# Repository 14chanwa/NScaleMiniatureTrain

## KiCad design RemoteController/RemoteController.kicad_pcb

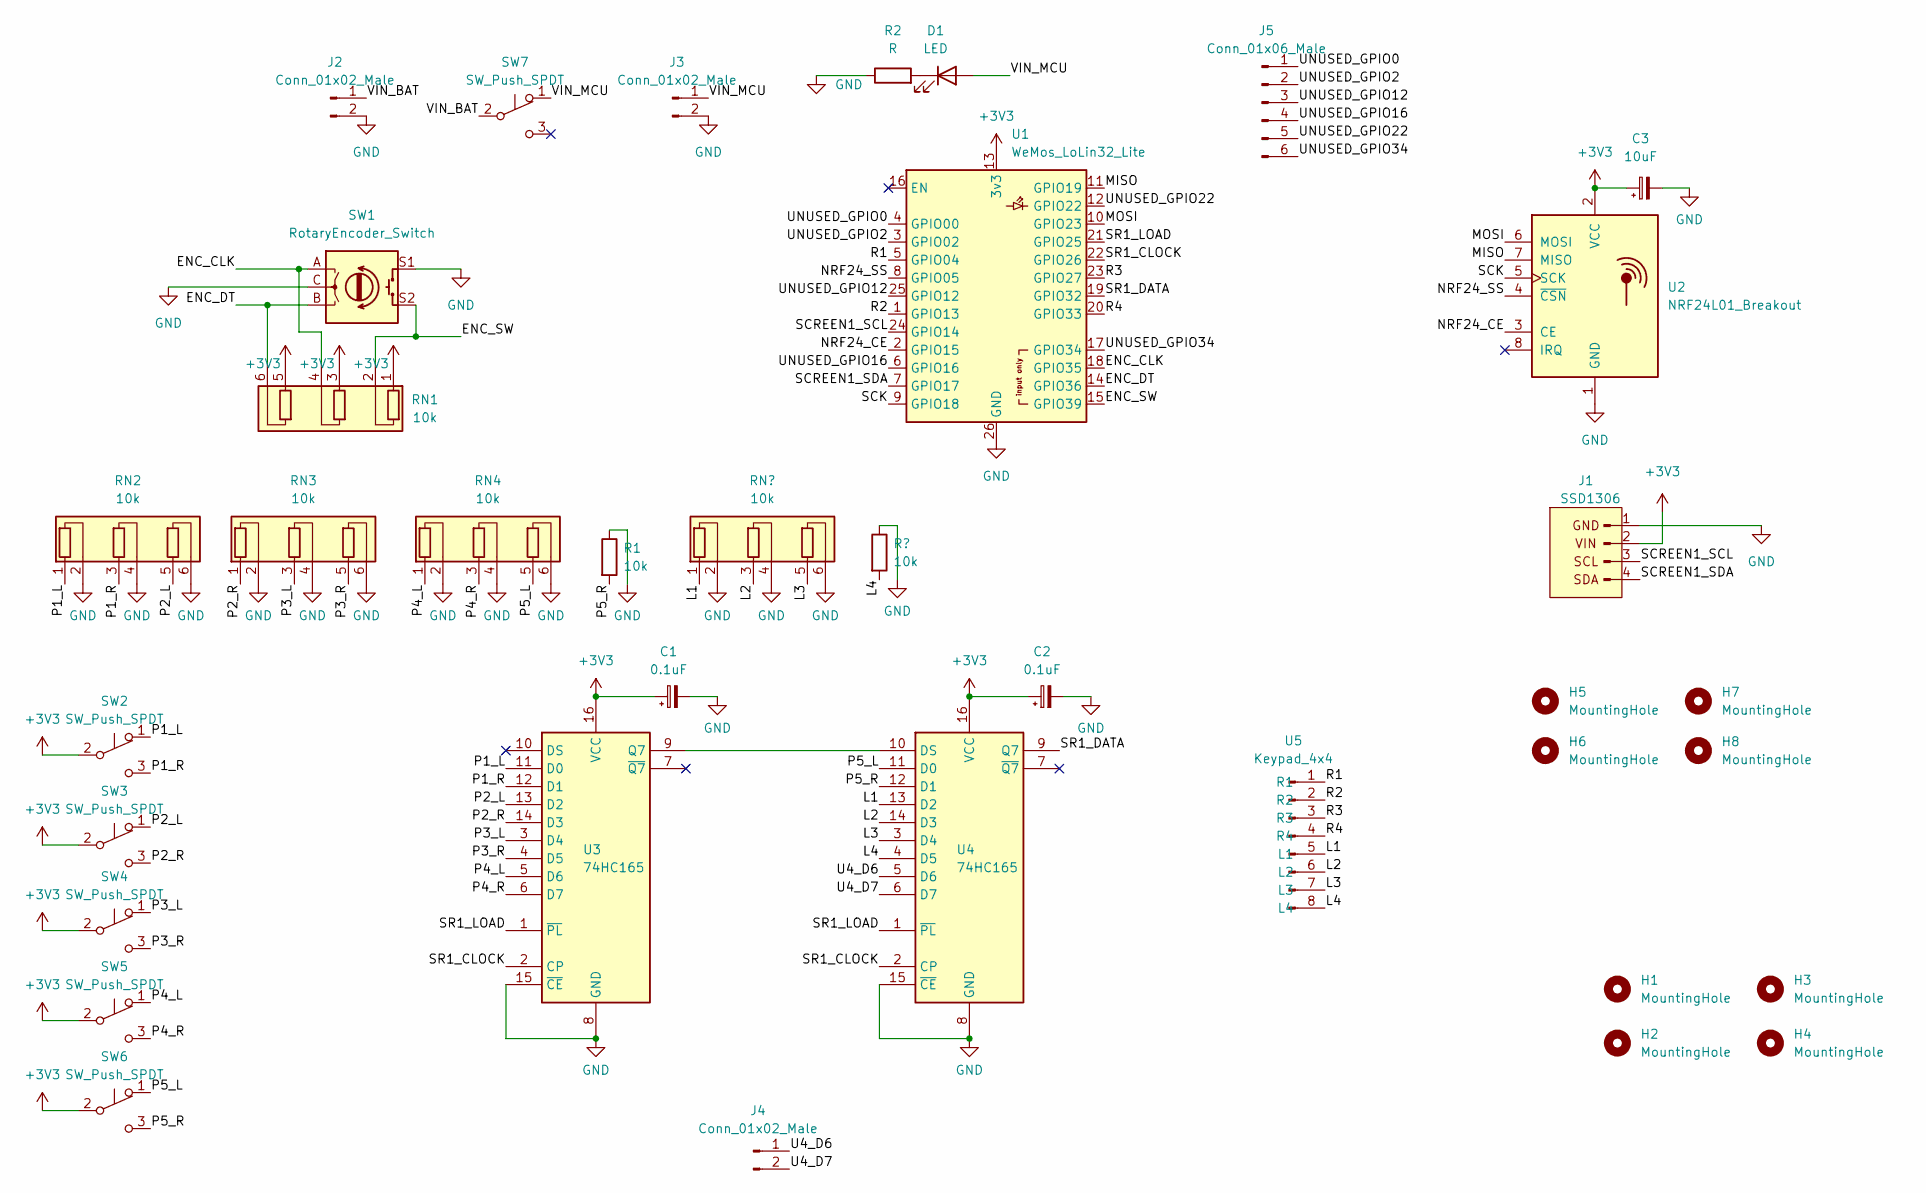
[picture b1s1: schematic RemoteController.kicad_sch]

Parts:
C1, C2: 0.1uF; CP_Radial_D4.0mm_P2.00mm
C3: 10uF; CP_Radial_D4.0mm_P2.00mm
D1: LED; LED_D3.0mm
H1, H2, H3, H4: MountingHole; MountingHole_2.5mm
H5, H6, H7, H8: MountingHole; MountingHole_4.3mm_M4_DIN965
J1: SSD1306; 128x64OLED
J2: Conn_01x02_Male; JST_PH_B2B-PH-K_1x02_P2.00mm_Vertical
J3: Conn_01x02_Male; PinHeader_1x02_P2.54mm_Vertical
J4: Conn_01x02_Male; PinSocket_1x02_P2.54mm_Vertical
J5: Conn_01x06_Male; PinSocket_1x06_P2.54mm_Vertical
R1: 10k; R_Axial_DIN0207_L6.3mm_D2.5mm_P10.16mm_Horizontal
R2: R; R_Axial_DIN0207_L6.3mm_D2.5mm_P10.16mm_Horizontal
RN1, RN2, RN3, RN4: 10k; R_Array_SIP6
SW1: RotaryEncoder_Switch; RotaryEncoder_Alps_EC12E-Switch_Vertical_H20mm
SW2, SW3, SW4, SW5, SW6, SW7: SW_Push_SPDT; Switch6mm
U1: WeMos_LoLin32_Lite; WEMOS_LoLin32_Lite
U2: NRF24L01_Breakout; nRF24L01_Breakout
U3, U4: 74HC165; SOP-16_4.4x10.4mm_P1.27mm
U5: Keypad_4x4; Keypad

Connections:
+3V3: C1.1, C2.1, C3.1, J1.2, RN1.1 (R1.1), RN1.3 (R2.1), RN1.5 (R3.1), SW2.2 (B), SW3.2 (B), SW4.2 (B), SW5.2 (B), SW6.2 (B), U1.13 (3v3), U2.2 (VCC), U3.16 (VCC), U4.16 (VCC)
/ENC_CLK: RN1.4 (R2.2), SW1.A, U1.18 (GPIO35)
/ENC_DT: RN1.6 (R3.2), SW1.B, U1.14 (GPIO36)
/ENC_SW: RN1.2 (R1.2), SW1.S2, U1.15 (GPIO39)
/L1: U4.13 (D2), U5.5 (L1); also elsewhere on the board
/L2: U4.14 (D3), U5.6 (L2); also elsewhere on the board
/L3: U4.3 (D4), U5.7 (L3); also elsewhere on the board
/L4: U4.4 (D5), U5.8 (L4); also elsewhere on the board
/MISO: U1.11 (GPIO19), U2.7 (MISO)
/MOSI: U1.10 (GPIO23), U2.6 (MOSI)
/NRF24_CE: U1.2 (GPIO15), U2.3 (CE)
/NRF24_SS: U1.8 (GPIO05), U2.4 (~CSN)
/P1_L: RN2.1 (R1.1), SW2.1 (A), U3.11 (D0)
/P1_R: RN2.3 (R2.1), SW2.3 (C), U3.12 (D1)
/P2_L: RN2.5 (R3.1), SW3.1 (A), U3.13 (D2)
/P2_R: RN3.1 (R1.1), SW3.3 (C), U3.14 (D3)
/P3_L: RN3.3 (R2.1), SW4.1 (A), U3.3 (D4)
/P3_R: RN3.5 (R3.1), SW4.3 (C), U3.4 (D5)
/P4_L: RN4.1 (R1.1), SW5.1 (A), U3.5 (D6)
/P4_R: RN4.3 (R2.1), SW5.3 (C), U3.6 (D7)
/P5_L: RN4.5 (R3.1), SW6.1 (A), U4.11 (D0)
/P5_R: R1.2, SW6.3 (C), U4.12 (D1)
/R1: U1.5 (GPIO04), U5.1 (R1)
/R2: U1.1 (GPIO13), U5.2 (R2)
/R3: U1.23 (GPIO27), U5.3 (R3)
/R4: U1.20 (GPIO33), U5.4 (R4)
/SCK: U1.9 (GPIO18), U2.5 (SCK)
/SCREEN1_SCL: J1.3, U1.24 (GPIO14)
/SCREEN1_SDA: J1.4, U1.7 (GPIO17)
/SR1_CLOCK: U1.22 (GPIO26), U3.2 (CP), U4.2 (CP)
/SR1_DATA: U1.19 (GPIO32), U4.9 (Q7)
/SR1_LOAD: U1.21 (GPIO25), U3.1 (~PL), U4.1 (~PL)
/U4_D6: J4.1, U4.5 (D6)
/U4_D7: J4.2, U4.6 (D7)
/UNUSED_GPIO0: J5.1, U1.4 (GPIO00)
/UNUSED_GPIO2: J5.2, U1.3 (GPIO02)
/UNUSED_GPIO12: J5.3, U1.25 (GPIO12)
/UNUSED_GPIO16: J5.4, U1.6 (GPIO16)
/UNUSED_GPIO22: J5.5, U1.12 (GPIO22)
/UNUSED_GPIO34: J5.6, U1.17 (GPIO34)
/VIN_BAT: J2.1, SW7.2 (B)
/VIN_MCU: D1.2 (A), J3.1, SW7.1 (A)
GND: C1.2, C2.2, C3.2, J1.1, J2.2, J3.2, R1.1, R2.1, RN2.2 (R1.2), RN2.4 (R2.2), RN2.6 (R3.2), RN3.2 (R1.2), RN3.4 (R2.2), RN3.6 (R3.2), RN4.2 (R1.2), RN4.4 (R2.2), RN4.6 (R3.2), SW1.C, SW1.S1, U1.26 (GND), U2.1 (GND), U3.8 (GND), U3.15 (~CE), U4.8 (GND), U4.15 (~CE); also elsewhere on the board
unnamed: D1.1 (K), R2.2
unnamed: U3.9 (Q7), U4.10 (DS)

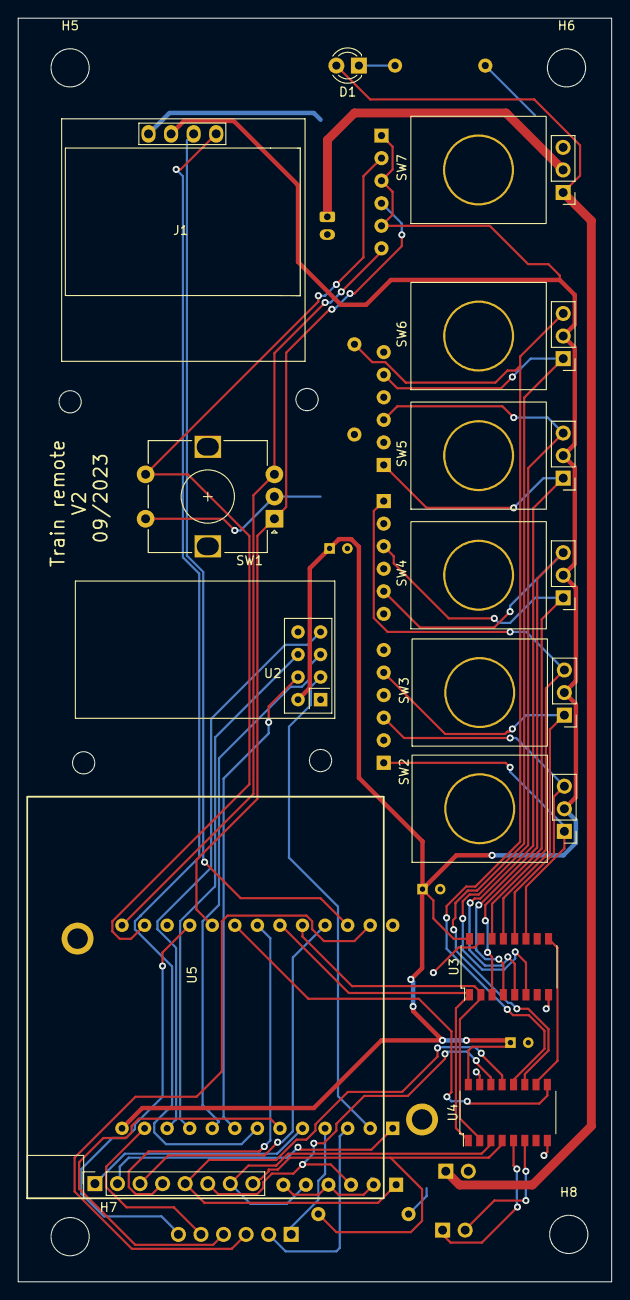
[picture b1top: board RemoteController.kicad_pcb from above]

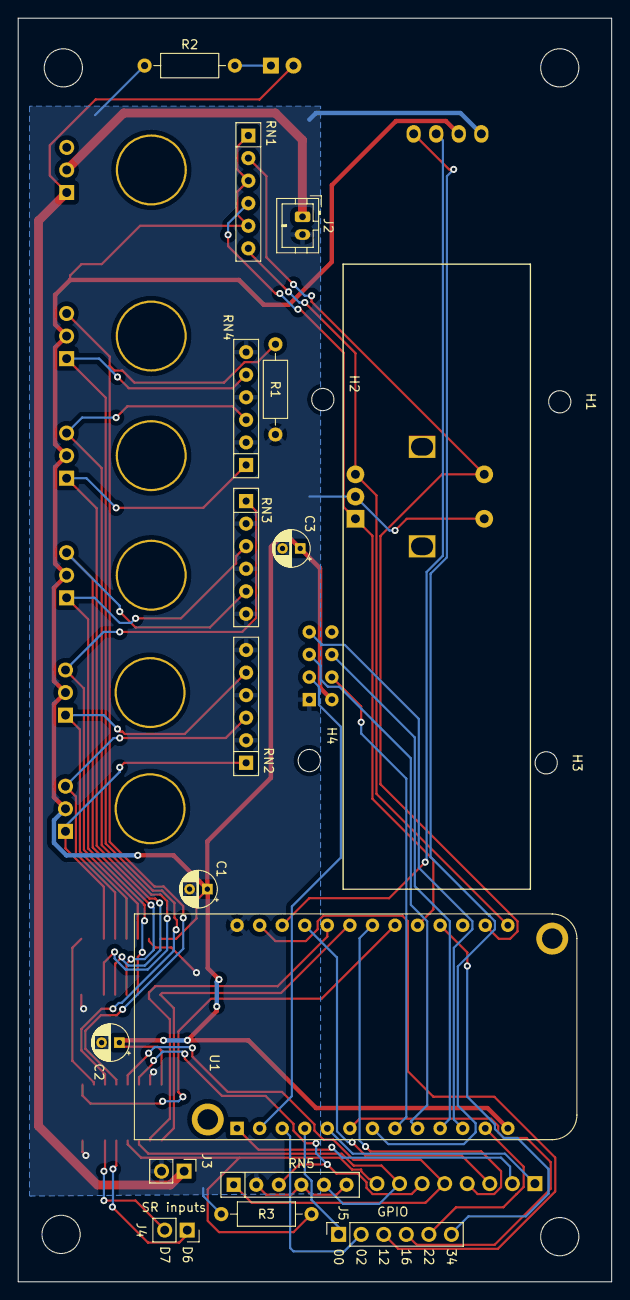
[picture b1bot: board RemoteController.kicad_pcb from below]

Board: 2 copper layers, 66.8 x 142.2 mm, 37 parts (20 on the bottom side), 45 nets.

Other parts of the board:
R3: 10k; R_Axial_DIN0207_L6.3mm_D2.5mm_P10.16mm_Horizontal
RN5: 10k; R_Array_SIP6

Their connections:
/L1: RN5.1 (R1.1); also elsewhere on the board
/L2: RN5.3 (R2.1); also elsewhere on the board
/L3: RN5.5 (R3.1); also elsewhere on the board
/L4: R3.2; also elsewhere on the board
GND: R3.1, RN5.2 (R1.2), RN5.4 (R2.2), RN5.6 (R3.2); also elsewhere on the board

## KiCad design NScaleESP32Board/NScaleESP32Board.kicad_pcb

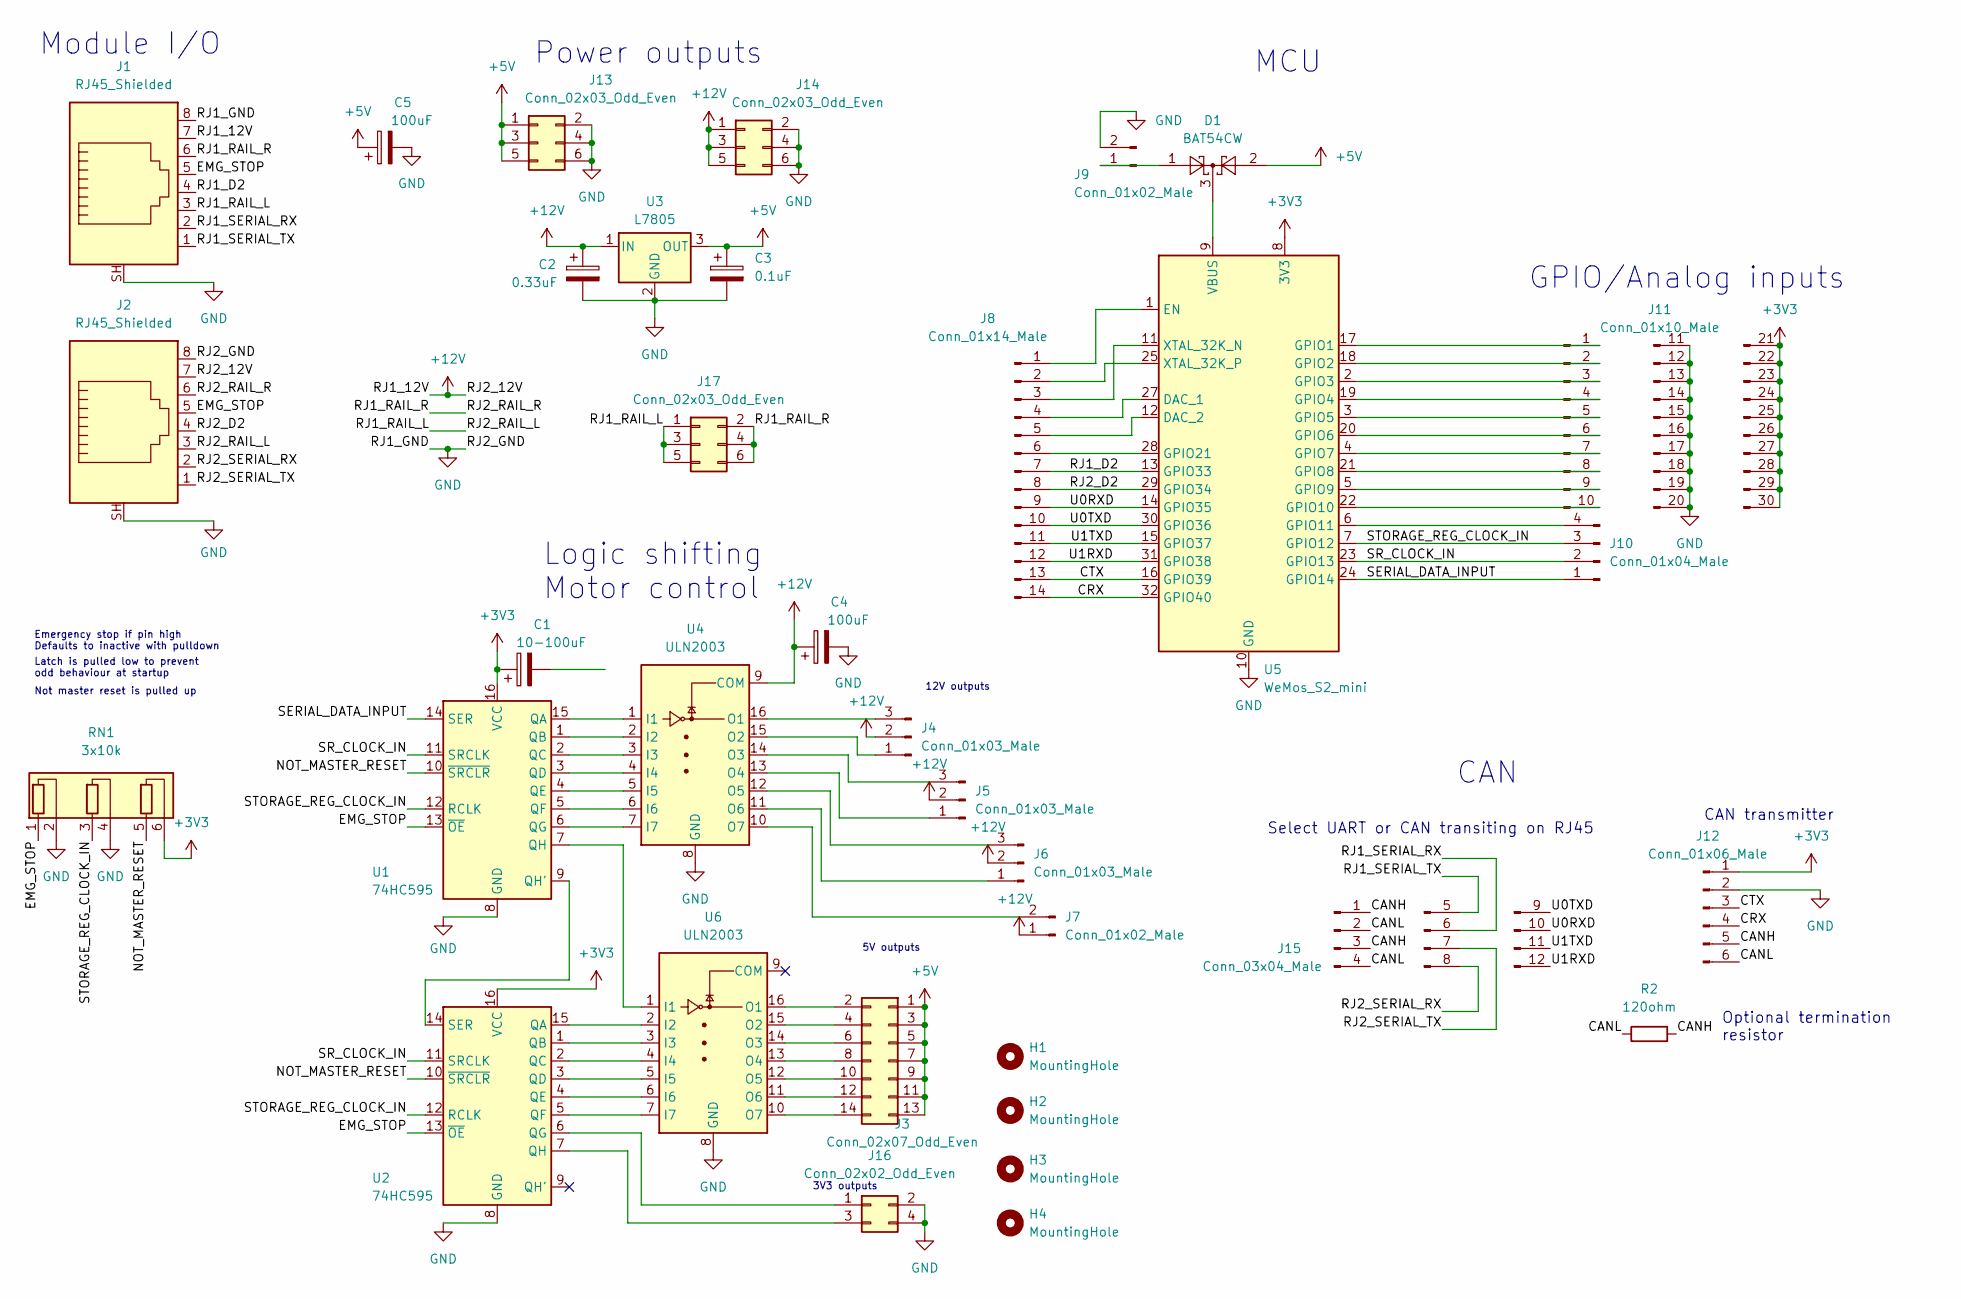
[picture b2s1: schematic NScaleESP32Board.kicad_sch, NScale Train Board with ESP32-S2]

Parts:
C1: 10-100uF; CP_Radial_D4.0mm_P2.00mm
C2: 0.33uF; CP_Radial_D4.0mm_P1.50mm
C3: 0.1uF; CP_Radial_D4.0mm_P1.50mm
C4, C5: 100uF; CP_Radial_D4.0mm_P2.00mm
D1: BAT54CW; SOT-323_SC-70
H1, H2, H3, H4: MountingHole; MountingHole_4.5mm
J1, J2: RJ45_Shielded; RJ45_Amphenol_RJHSE5380
J3: Conn_02x07_Odd_Even; PinHeader_2x07_P2.54mm_Vertical
J4, J5, J6: Conn_01x03_Male; PinHeader_1x03_P2.54mm_Vertical
J7, J9: Conn_01x02_Male; PinHeader_1x02_P2.54mm_Vertical
J8: Conn_01x14_Male; PinHeader_1x14_P2.54mm_Vertical
J10: Conn_01x04_Male; PinHeader_1x04_P2.54mm_Vertical
J11: Conn_01x10_Male; PinHeader_3x10_P2.54mm_Vertical
J12: Conn_01x06_Male; PinHeader_1x06_P2.54mm_Vertical
J13, J14, J17: Conn_02x03_Odd_Even; PinHeader_2x03_P2.54mm_Vertical
J15: Conn_03x04_Male; PinHeader_3x4_P2.54mm_Vertical
J16: Conn_02x02_Odd_Even; PinHeader_2x02_P2.54mm_Vertical
R2: 120ohm; R_Axial_DIN0207_L6.3mm_D2.5mm_P10.16mm_Horizontal
RN1: 3x10k; R_Array_SIP6
U1, U2: 74HC595; DIP-16_W7.62mm
U3: L7805; TO-220-3_Horizontal_TabDown
U4, U6: ULN2003; DIP-16_W7.62mm
U5: WeMos_S2_mini; WEMOS_S2_mini

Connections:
+3V3: C1.1, J11.21, J11.22, J11.23, J11.24, J11.25, J11.26, J11.27, J11.28, J11.29, J11.30, J12.1, RN1.6 (R3.2), U1.16 (VCC), U2.16 (VCC), U5.8 (3V3)
+12V: C2.1, C4.1, J1.7, J2.7, J4.2, J5.2, J6.2, J7.1, J14.1, J14.3, J14.5, U3.1 (IN), U4.9 (COM)
/CANH: J12.5, J15.1, J15.3, R2.2
/CANL: J12.6, J15.2, J15.4, R2.1
/CRX: J8.14, J12.4, U5.32 (GPIO40)
/CTX: J8.13, J12.3, U5.16 (GPIO39)
/EMG_STOP: J1.5, J2.5, RN1.1 (R1.1), U1.13 (~OE), U2.13 (~OE)
/NOT_MASTER_RESET: RN1.5 (R3.1), U1.10 (~SRCLR), U2.10 (~SRCLR)
/RJ1_D2: J1.4, J8.7, U5.13 (GPIO33)
/RJ1_RAIL_L: J1.3, J2.3, J17.1, J17.3, J17.5
/RJ1_RAIL_R: J1.6, J2.6, J17.2, J17.4, J17.6
/RJ1_SERIAL_RX: J1.2, J15.6
/RJ1_SERIAL_TX: J1.1, J15.5
/RJ2_D2: J2.4, J8.8, U5.29 (GPIO34)
/RJ2_SERIAL_RX: J2.2, J15.8
/RJ2_SERIAL_TX: J2.1, J15.7
/SERIAL_DATA_INPUT: J10.1, U1.14 (SER), U5.24 (GPIO14)
/SR_CLOCK_IN: J10.2, U1.11 (SRCLK), U2.11 (SRCLK), U5.23 (GPIO13)
/STORAGE_REG_CLOCK_IN: J10.3, RN1.3 (R2.1), U1.12 (RCLK), U2.12 (RCLK), U5.7 (GPIO12)
/U0RXD: J8.9, J15.10, U5.14 (GPIO35)
/U0TXD: J8.10, J15.9, U5.30 (GPIO36)
/U1RXD: J8.12, J15.12, U5.31 (GPIO38)
/U1TXD: J8.11, J15.11, U5.15 (GPIO37)
GND: C2.2, C3.2, C4.2, C5.2, J1.8, J1.SH, J2.8, J2.SH, J9.2, J11.11, J11.12, J11.13, J11.14, J11.15, J11.16, J11.17, J11.18, J11.19, J11.20, J12.2, J13.2, J13.4, J13.6, J14.2, J14.4, J14.6, J16.2, J16.4, RN1.2 (R1.2), RN1.4 (R2.2), U1.8 (GND), U2.8 (GND), U3.2 (GND), U4.8 (GND), U5.10 (GND), U5.26 (GND), U6.8 (GND)
unnamed: D1.1, J9.1
unnamed: D1.3, U5.9 (VBUS)
unnamed: J5.3, U4.14 (O3)
unnamed: J8.1, U5.1 (EN)
unnamed: J8.2, U5.25 (XTAL_32K_P)
unnamed: J8.3, U5.11 (XTAL_32K_N)
unnamed: J8.4, U5.27 (DAC_1)
unnamed: J8.5, U5.12 (DAC_2)
unnamed: J8.6, U5.28 (GPIO21)
unnamed: J10.4, U5.6 (GPIO11)
unnamed: J11.1, U5.17 (GPIO1)
unnamed: J11.2, U5.18 (GPIO2)
unnamed: J11.3, U5.2 (GPIO3)
unnamed: J11.4, U5.19 (GPIO4)
unnamed: J11.5, U5.3 (GPIO5)
unnamed: J11.6, U5.20 (GPIO6)
unnamed: J11.7, U5.4 (GPIO7)
unnamed: J11.8, U5.21 (GPIO8)
unnamed: J11.9, U5.5 (GPIO9)
unnamed: J11.10, U5.22 (GPIO10)
unnamed: U1.1 (QB), U4.2 (I2)
unnamed: U1.2 (QC), U4.3 (I3)
unnamed: U1.3 (QD), U4.4 (I4)
unnamed: U1.4 (QE), U4.5 (I5)
unnamed: U1.5 (QF), U4.6 (I6)
unnamed: U1.6 (QG), U4.7 (I7)
unnamed: U1.7 (QH), U6.1 (I1)
unnamed: U1.9 (QH'), U2.14 (SER)
unnamed: U1.15 (QA), U4.1 (I1)
unnamed: U2.1 (QB), U6.3 (I3)
unnamed: U2.2 (QC), U6.4 (I4)
unnamed: U2.3 (QD), U6.5 (I5)
unnamed: U2.4 (QE), U6.6 (I6)
unnamed: U2.5 (QF), U6.7 (I7)
unnamed: J16.1, U2.6 (QG)
unnamed: J16.3, U2.7 (QH)
unnamed: U2.15 (QA), U6.2 (I2)
unnamed: J7.2, U4.10 (O7)
unnamed: J6.1, U4.11 (O6)
unnamed: J6.3, U4.12 (O5)
unnamed: J5.1, U4.13 (O4)
unnamed: J4.1, U4.15 (O2)
unnamed: J4.3, U4.16 (O1)
unnamed: J3.14, U6.10 (O7)
unnamed: J3.12, U6.11 (O6)
unnamed: J3.10, U6.12 (O5)
unnamed: J3.8, U6.13 (O4)
unnamed: J3.6, U6.14 (O3)
unnamed: J3.4, U6.15 (O2)
unnamed: J3.2, U6.16 (O1)

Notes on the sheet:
GPIO/Analog inputs
Select UART or CAN transiting on RJ45
3V3 outputs
MCU
Module I/O
Power outputs
Optional termination resistor
5V outputs
Emergency stop if pin high Defaults to inactive with pulldown
Not master reset is pulled up
Latch is pulled low to prevent odd behaviour at startup
CAN
CAN transmitter
Logic shifting Motor control
12V outputs

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
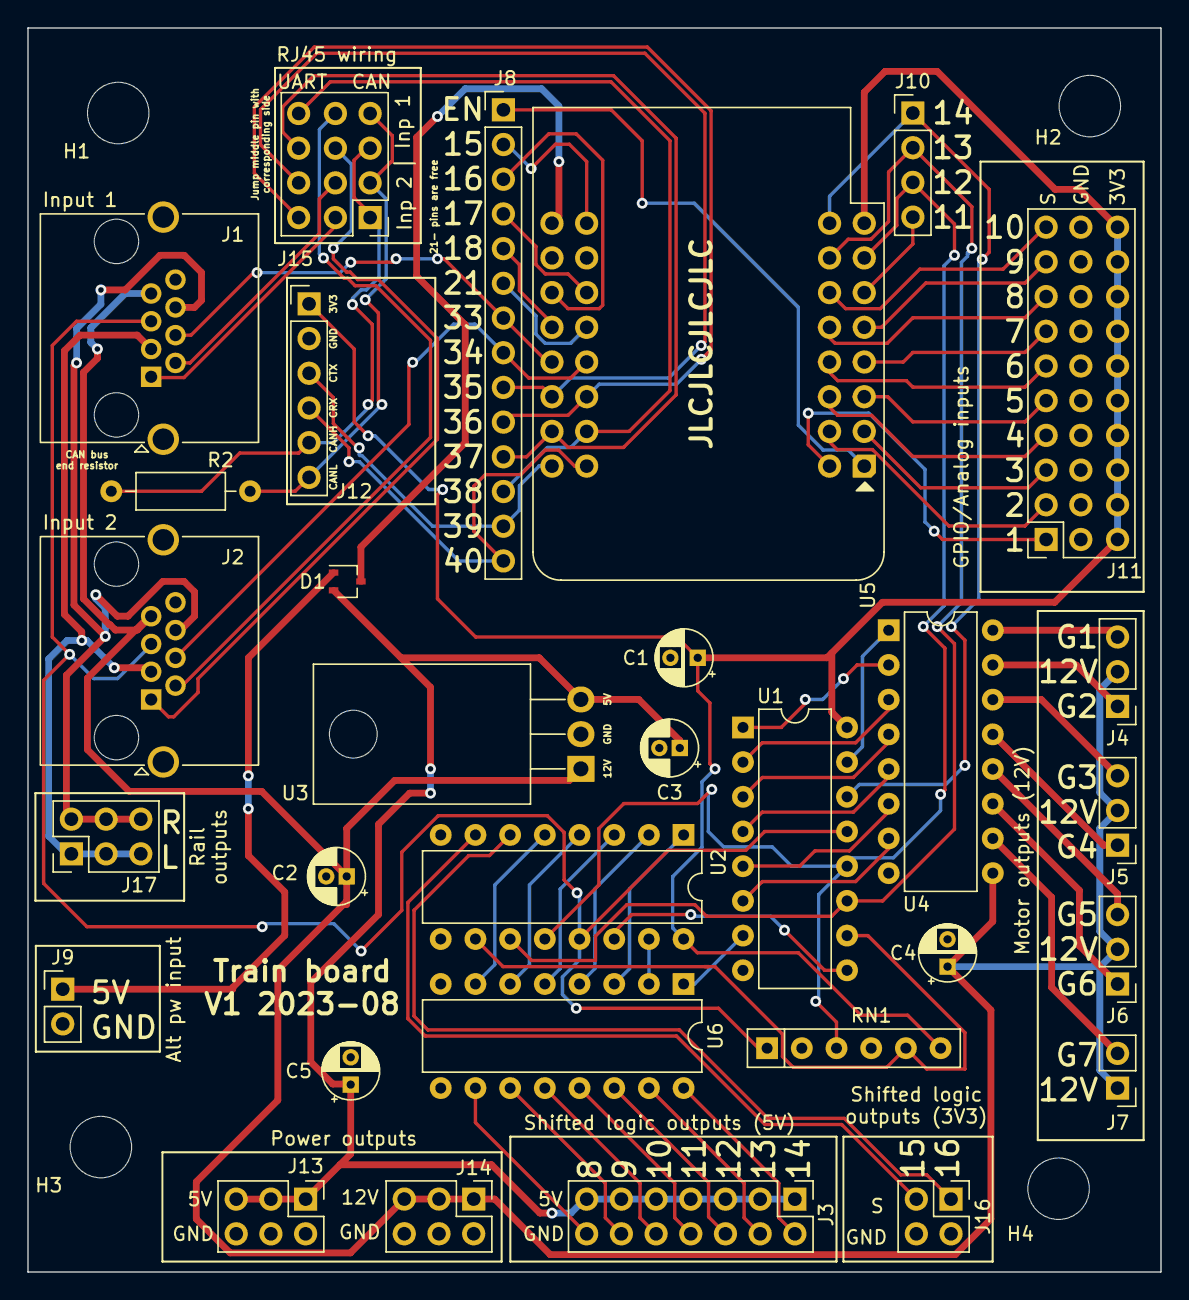
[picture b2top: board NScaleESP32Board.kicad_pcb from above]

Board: 2 copper layers, 82.9 x 91.1 mm, 35 parts (0 on the bottom side), 75 nets.

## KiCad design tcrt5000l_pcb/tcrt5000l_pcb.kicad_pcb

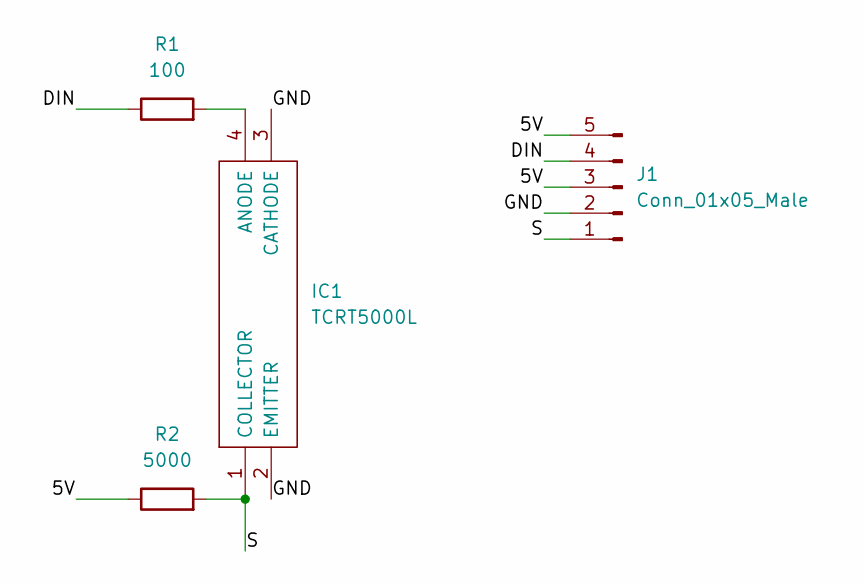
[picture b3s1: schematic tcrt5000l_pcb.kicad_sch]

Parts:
IC1: TCRT5000L; Manufacturer_Part_Number TCRT5000L; Mouser Part Number 782-TCRT5000L
J1: Conn_01x05_Male; PinHeader_1x05_P2.54mm_Vertical
R1: 100; R_0805_2012Metric
R2: 5000; R_0805_2012Metric

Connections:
/5V: J1.3, J1.5, R2.1
/DIN: J1.4, R1.1
/GND: IC1.2 (EMITTER), IC1.3 (CATHODE), J1.2
/S: IC1.1 (COLLECTOR), J1.1, R2.2
unnamed: IC1.4 (ANODE), R1.2

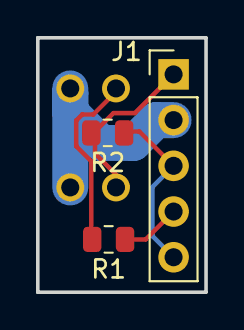
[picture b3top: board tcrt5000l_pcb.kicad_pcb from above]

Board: 2 copper layers, 9.3 x 14.1 mm, 4 parts (1 on the bottom side), 5 nets.

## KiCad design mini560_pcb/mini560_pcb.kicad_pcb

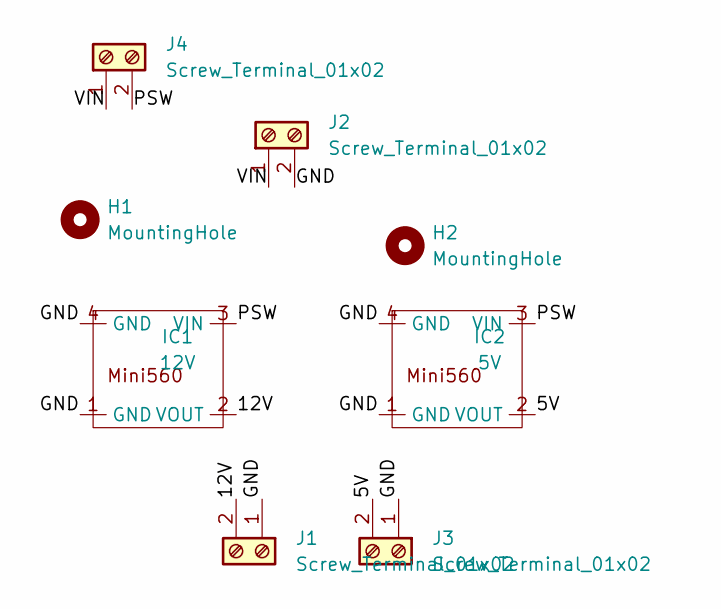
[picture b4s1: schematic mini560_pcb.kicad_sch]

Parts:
H1, H2: MountingHole; MountingHole_3.2mm_M3
IC1: 12V; Mini560
IC2: 5V; Mini560
J1, J2, J3, J4: Screw_Terminal_01x02; TerminalBlock_bornier-2_P5.08mm

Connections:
/5V: IC2.2 (VOUT), J3.2
/12V: IC1.2 (VOUT), J1.2
/GND: IC1.1 (GND), IC1.4 (GND), IC2.1 (GND), IC2.4 (GND), J1.1, J2.2, J3.1
/PSW: IC1.3 (VIN), IC2.3 (VIN), J4.2
/VIN: J2.1, J4.1

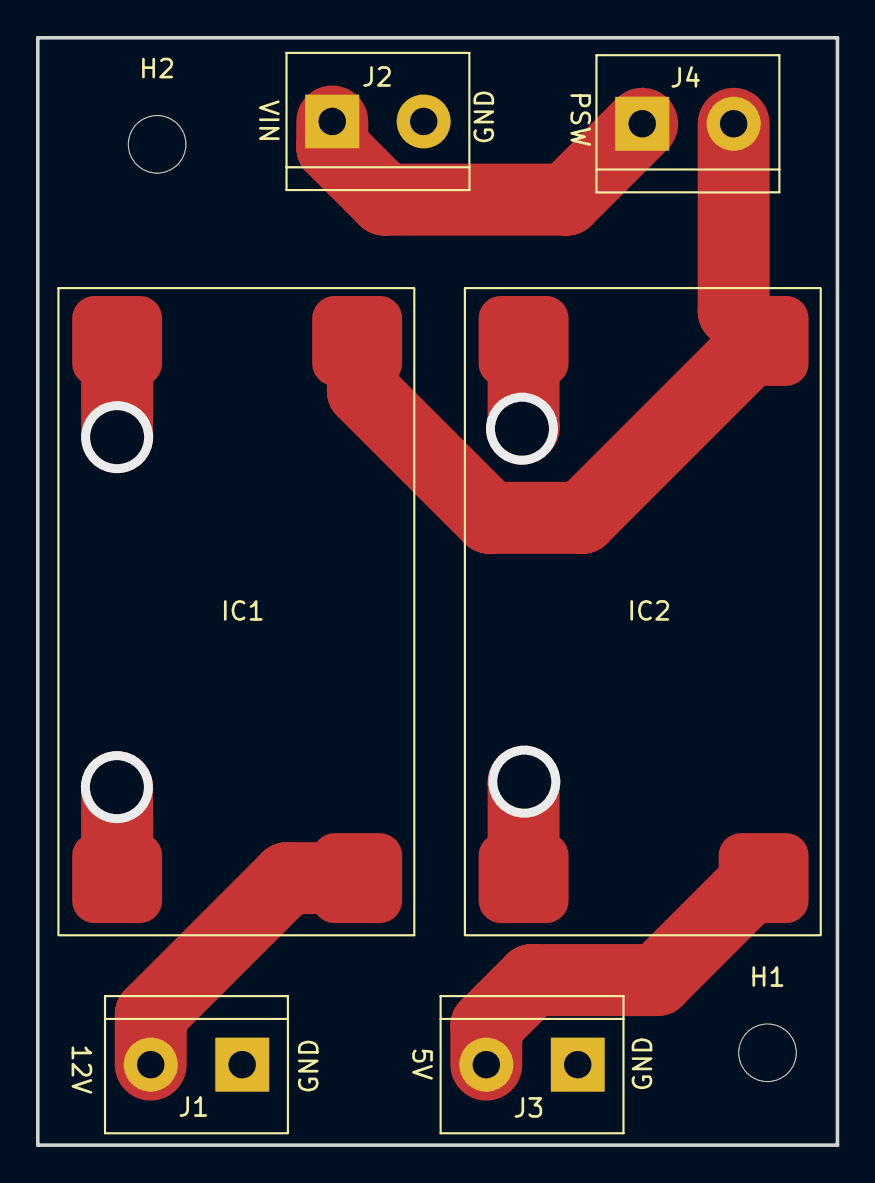
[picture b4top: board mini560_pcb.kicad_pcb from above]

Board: 2 copper layers, 44.4 x 61.5 mm, 8 parts (0 on the bottom side), 5 nets.

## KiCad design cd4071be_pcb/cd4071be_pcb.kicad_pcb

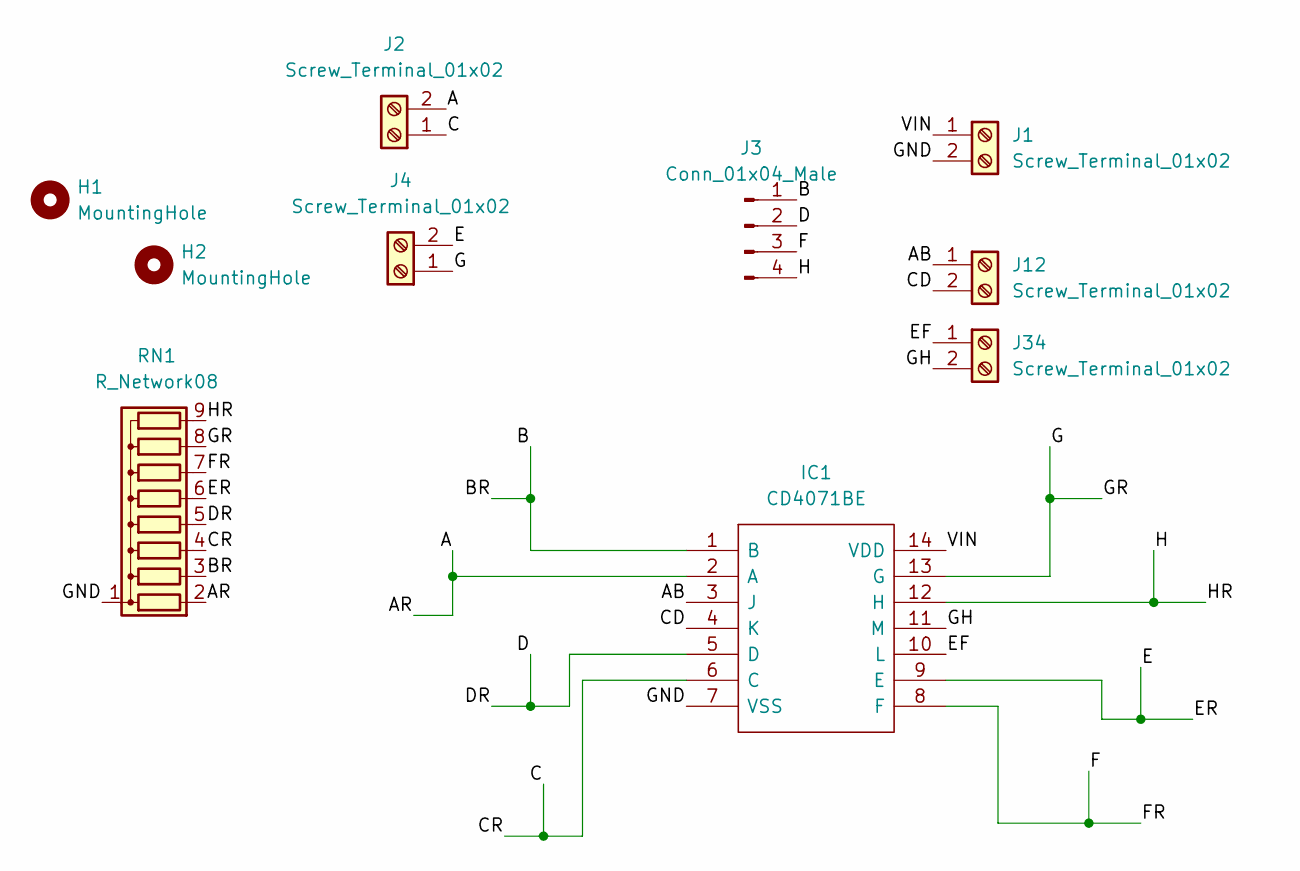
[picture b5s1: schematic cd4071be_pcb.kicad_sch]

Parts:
H1, H2: MountingHole; MountingHole_3.2mm_M3
IC1: CD4071BE; DIP794W53P254L1930H508Q14N; Manufacturer_Part_Number CD4071BE; Mouser Part Number 595-CD4071BE
J1, J2, J4, J12, J34: Screw_Terminal_01x02; TerminalBlock_bornier-2_P5.08mm
J3: Conn_01x04_Male; PinHeader_1x04_P2.54mm_Vertical
RN1: R_Network08; R_Array_SIP9

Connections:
/A: IC1.2 (A), J2.2, RN1.2 (R1)
/AB: IC1.3 (J), J12.1
/B: IC1.1 (B), J3.1, RN1.3 (R2)
/C: IC1.6 (C), J2.1, RN1.4 (R3)
/CD: IC1.4 (K), J12.2
/D: IC1.5 (D), J3.2, RN1.5 (R4)
/E: IC1.9 (E), J4.2, RN1.6 (R5)
/EF: IC1.10 (L), J34.1
/F: IC1.8 (F), J3.3, RN1.7 (R6)
/G: IC1.13 (G), J4.1, RN1.8 (R7)
/GH: IC1.11 (M), J34.2
/GND: IC1.7 (VSS), J1.2, RN1.1 (common)
/H: IC1.12 (H), J3.4, RN1.9 (R8)
/VIN: IC1.14 (VDD), J1.1

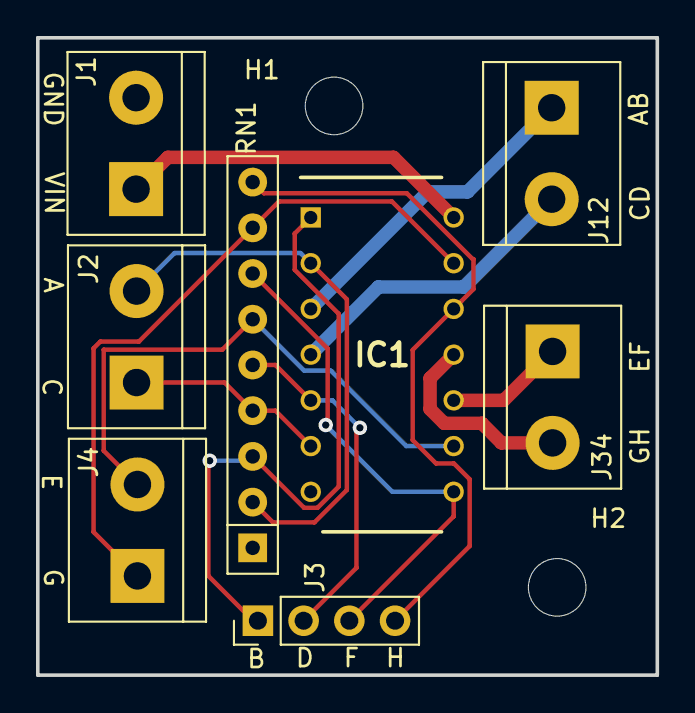
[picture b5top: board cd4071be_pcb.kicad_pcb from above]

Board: 2 copper layers, 34.4 x 35.4 mm, 10 parts (0 on the bottom side), 14 nets.

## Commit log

2023-01-15 Add CD4071BE PCB
2023-01-15 Add mini560 PCB
2023-01-15 Add TCRT5000L PCB
2023-08-28 Add new train boards
2023-09-08 Add TrainRemote PCB
2023-09-08 Add TrainRemote code
2023-09-15 Update code with buttons
2023-09-15 Fix Remote PCB for future version
